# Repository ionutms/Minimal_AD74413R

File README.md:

# Minimal_AD74413R

## Overview

This repository contains a minimal KiCad design project for the Analog Devices AD74413R, a quad-channel, software-configurable input and output device. The project includes schematic designs and PCB layout files for implementing this versatile analog I/O device.

## Disclaimer

> [!NOTE]
> This project is provided "as is" and without any warranty, express or implied. For more details, please see the [LICENSE](LICENSE) file.

## About the AD74413R

The AD74413R from Analog Devices is a quad-channel, software-configurable input/output solution for building and process control applications. It integrates a 16-bit, sigma-delta (Σ-Δ) analog-to-digital converter (ADC) and four 13-bit digital-to-analog converters (DACs).

Key features include:

- **Software-Configurable Channels:** Each of the four channels can be independently configured as:
  - Analog Input (Voltage or Current)
  - Analog Output (Voltage or Current)
  - Digital Input
  - Resistance Temperature Detector (RTD) and Thermocouple measurements
- **Multiple Operating Modes:**
  - Voltage Output: 0 V to 10 V
  - Current Output: 0 mA to 24 mA
  - Voltage Input: ±10 V
  - Current Input: 0 mA to 24 mA (externally powered and loop-powered)
  - Digital Input: Logic and loop-powered
- **High Accuracy:** Includes a high-accuracy 2.5V internal reference.
- **Robustness and Diagnostics:** Features on-chip diagnostics like open-circuit and short-circuit detection.
- **HART Compatibility:** Compatible with HART (Highway Addressable Remote Transducer) protocol.
- **Communication:** Uses a Serial Peripheral Interface (SPI) for configuration and data transfer.
- **Operating Temperature Range:** -40°C to +105°C.

## Project Structure

```
minimal_ad74413r/
├── minimal_ad74413r.kicad_sch       # Main schematic file
├── minimal_ad74413r.kicad_pcb       # PCB layout file
├── minimal_ad74413r.kicad_pro       # Project configuration file
├── fp-lib-table                     # Footprint library table
├── sym-lib-table                    # Symbol library table
├── Front End Channel 1.kicad_sch    # Channel-specific schematic
├── project_jobs_set.kicad_jobset    # Project job settings
├── ibom.config.ini                  # Interactive BOM configuration
├── docs/                            # Documentation files
│   ├── pictures/                    # Images and photos
│   ├── schematics/                  # Schematic PDF exports
│   └── 3d_models/                   # 3D model files
└── KiCAD_Symbols_Generator/         # Submodule for symbol generation from CSV data
```

## Project Features

This design provides a minimal implementation of the AD74413R with the following features:

- **Power Supply:**
  - AVDD: +24V
  - AVSS: -24V
  - IOVDD: +3.3V
  - AVDD_REG and DVDD_REG: +1.8V (internally regulated)
- **Channel Configuration:**
  - Basic protection circuits for each of the four I/O channels.
  - Support for all operating modes of the AD74413R.
- **Bill of Materials (BOM):**
  - Interactive HTML BOM (`ibom.html`) for easy component identification and sourcing.
- **Libraries:**
  - Comprehensive symbol and footprint libraries integrated as a submodule.
- **3D Model:**
  - Includes a 3D model of the board for better visualization.

## Getting Started

### Prerequisites

- [KiCad EDA](https://www.kicad.org/) version 9.0 or later installed on your system
- Git (for cloning the repository and submodule management)

### Opening the Project

1. **Clone the repository** (including submodules):
   ```bash
   git clone --recursive https://github.com/ionutms/Minimal_AD74413R.git
   ```
   
   If you've already cloned the repository without submodules, initialize them with:
   ```bash
   git submodule init
   git submodule update
   ```

2. **Open the project in KiCad**:
   - Launch KiCad
   - Click "Open Existing Project"
   - Navigate to the cloned repository folder
   - Select the `minimal_ad74413r.kicad_pro` file

3. **Explore the design**:
   - Open the schematic editor to view the circuit design
   - Open the PCB editor to view the board layout
   - Review the symbol and footprint libraries used in the design

### Project Files

- **Main schematic**: `minimal_ad74413r.kicad_sch` - Contains the primary circuit design with the AD74413R and support components
- **Channel schematic**: `Front End Channel 1.kicad_sch` - Detailed implementation of one channel with protection and filtering
- **PCB layout**: `minimal_ad74413r.kicad_pcb` - Physical board design file with proper component placement
- **Project configuration**: `minimal_ad74413r.kicad_pro` - KiCad project settings

## Dependencies

This project has the following dependencies:

### 1. KiCAD Symbols Generator

This repository uses [KiCAD_Symbols_Generator](https://github.com/ionutms/KiCAD_Symbols_Generator) as a submodule for custom symbol generation.

To initialize the submodule after cloning this repository:

```bash
git submodule update --init --recursive
```

### 2. 3D Models

This project requires the [3D_Models_Vault](https://github.com/ionutms/3D_Models_Vault) repository for 3D models.

#### Setup for KiCAD 9:

1. Clone the 3D models repository:
   ```bash
   git clone https://github.com/ionutms/3D_Models_Vault.git
   ```

2. In KiCAD 9, add an environment variable:
   - Variable name: `KICAD9_3D_MODELS_VAULT`
   - Variable value: Full path to where you cloned the 3D_Models_Vault repository

## Usage

After setting up the dependencies, open the project in KiCad 9 to access all features including the 3D models.

## Symbol Generator Submodule

This project includes the KiCAD_Symbols_Generator as a submodule, which provides tools for generating KiCad symbols from CSV data files. For more information on using this tool, see the [KiCAD_Symbols_Generator documentation](minimal_ad74413r/KiCAD_Symbols_Generator/README.md).

## Documentation

The `docs` folder contains:
- Schematic PDF exports
- Images and photos of the design
- 3D model files (GLB and WRL formats)

## Visuals

The following images showcase the PCB design from different perspectives:

*Top View of the PCB*

*Side View of the PCB*

*Bottom View of the PCB*

## License

This project is licensed under the MIT License - see the [LICENSE](LICENSE) file for details.

## References

- [AD74413R Datasheet](https://www.analog.com/media/en/technical-documentation/data-sheets/ad74413r.pdf)
- [KiCad EDA](https://www.kicad.org/)

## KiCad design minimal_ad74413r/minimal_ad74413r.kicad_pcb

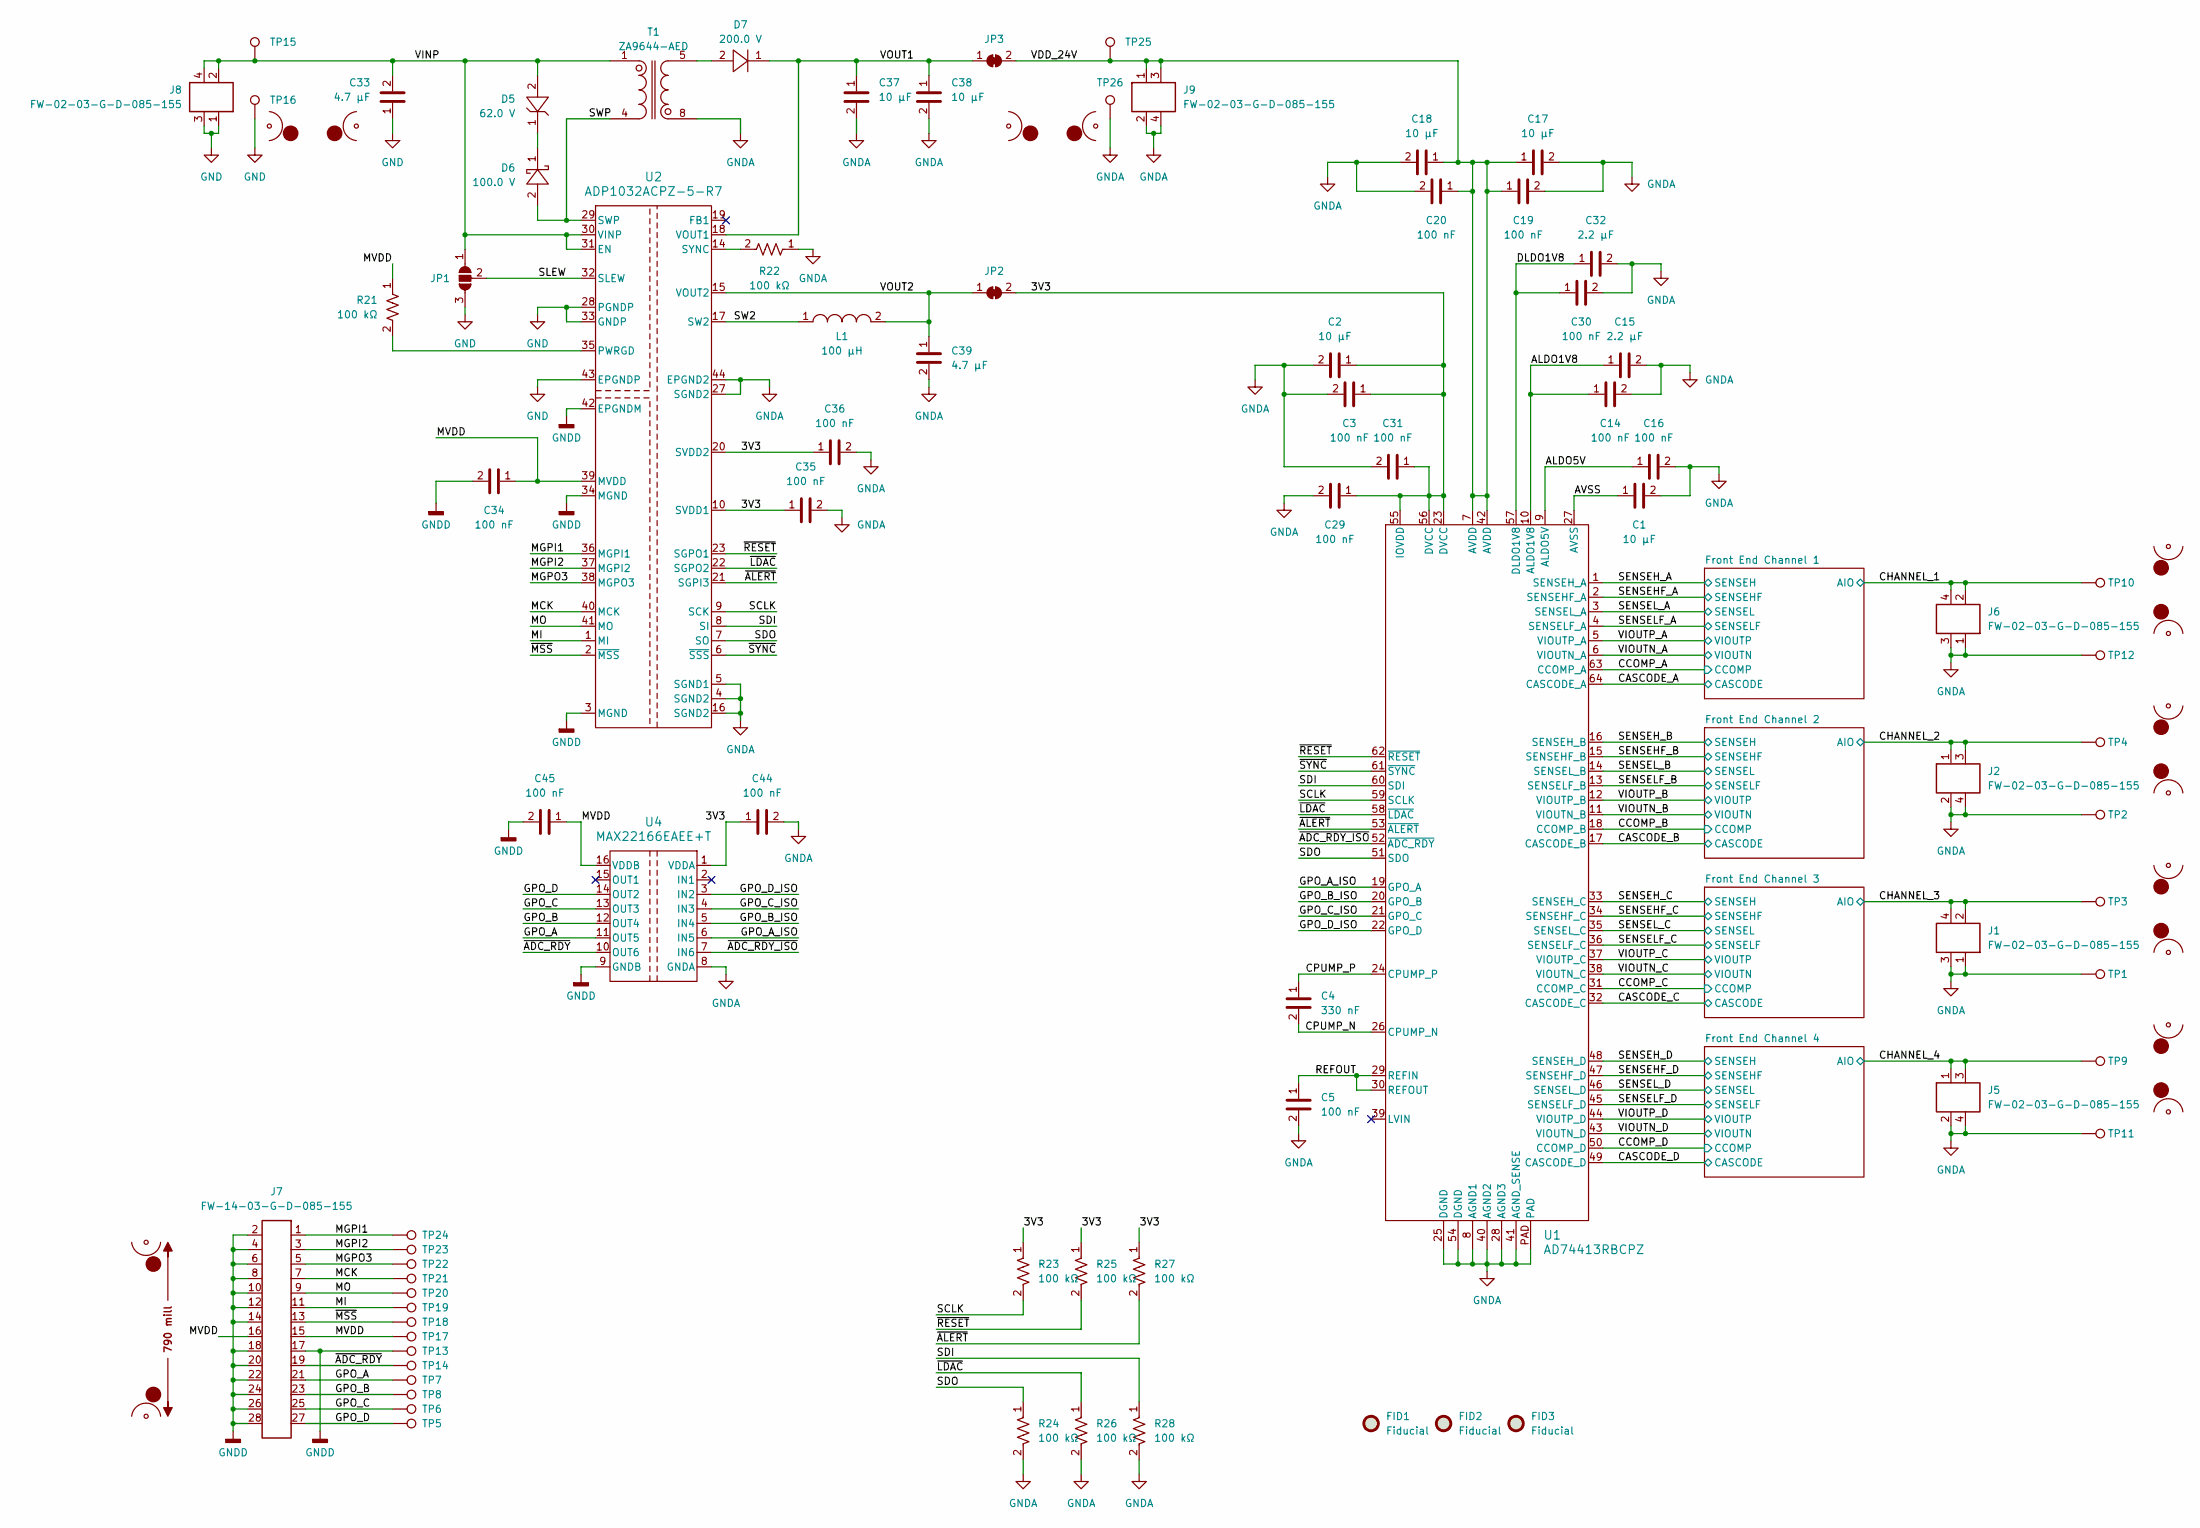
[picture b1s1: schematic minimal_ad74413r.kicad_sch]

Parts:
C1, C2, C17, C18, C37, C38: 10 µF; C_1206_3216Metric; Voltage Rating DC 50 VDC; Tolerance 10%; MPN CL31B106KBHNNN#
C3, C5, C14, C16, C19, C20, C29, C30, C31, C34, C35, C36, C44, C45: 100 nF; C_0402_1005Metric; Voltage Rating DC 50 VDC; Tolerance 10%; MPN GCM155R71H104KE02D
C4: 330 nF; C_0603_1608Metric; Voltage Rating DC 10 VDC; Tolerance 10%; MPN GRM188R71A334KA61D
C15, C32: 2.2 µF; C_0402_1005Metric; Voltage Rating DC 10 VDC; Tolerance 10%; MPN GRM155Z71A225KE44D
C33: 4.7 µF; C_1210_200_3225Metric; Tolerance 10%; Voltage Rating 100V; MPN GCM32DC72A475KE02K
C39: 4.7 µF; C_0603_1608Metric; Voltage Rating DC 10 VDC; Tolerance 10%; MPN C1608X7S1A475K080AC
D5: 62.0 V; SOD_123; MPN MMSZ5265BT1G
D6: 100.0 V; PowerDI_123; MPN DFLS1200-7
D7: 200.0 V; SOD_123F; MPN US1DWF
FID1, FID2, FID3: Fiducial; Fiducial_0.5mm_Mask1mm
J1, J2, J5, J6, J8, J9: FW-02-03-G-D-085-155; Current Rating (A) 5.2; Voltage Rating (V) 300; MPN FW-02-03-G-D-085-155
J7: FW-14-03-G-D-085-155; Current Rating (A) 5.2; Voltage Rating (V) 300; MPN FW-14-03-G-D-085-155
JP1: SolderJumper_3_Open; SolderJumper-3_P1.3mm_Open_RoundedPad1.0x1.5mm_NumberLabels
JP2, JP3: SolderJumper_2_Bridged; SolderJumper-2_P1.3mm_Bridged_RoundedPad1.0x1.5mm
L1: 100 µH; XFL3012; Tolerance ±20%; MPN XFL3012-104ME
MB1, MB2, MB5, MB6, MB8, MB9: mouse-bite-midle-50mil-200mil
MB7: mouse-bite-midle-50mil-200mil; mouse-bite-50mil-790mil
R21, R22, R23, R24, R25, R26, R27, R28: 100 kΩ; R_0402_1005Metric; Voltage Rating 50V; Tolerance 5%; MPN ERJ-2GEJ104X
T1: ZA9644-AED; ZA9644; Tolerance ±10%; MPN ZA9644-AED
TP1, TP2, TP3, TP4, TP5, TP6, TP7, TP8, TP9, TP10, TP11, TP12, TP13, TP14, TP15, TP16, TP17, TP18, TP19, TP20, TP21, TP22, TP23, TP24, TP25, TP26: TestPoint; TestPoint_THTPad_Castelated
U1: AD74413RBCPZ; CP-64-15_ADI; MPN AD74413RBCPZ
U2: ADP1032ACPZ-5-R7; CP-41-1_ADI; MPN ADP1032ACPZ-5-R7
U4: MAX22166EAEE+T; 21-0055_E16MS&plus_2_MXM_ADI; MPN MAX22166EAEE+T

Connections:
/3V3: C2.1, C3.1, C29.1, C31.1, C35.1, C36.1, C44.1, JP2.2, R23.1, R25.1, R27.1, U1.23 (DVCC), U1.55 (IOVDD), U1.56 (DVCC), U2.10 (SVDD1), U2.20 (SVDD2), U4.1 (VDDA)
/ALDO1V8: C14.1, C15.1, U1.10 (ALDO1V8)
/ALDO5V: C16.1, U1.9 (ALDO5V)
/AVSS: C1.1, U1.27 (AVSS)
/CASCODE_A: U1.64 (CASCODE_A); also elsewhere on the board
/CASCODE_B: U1.17 (CASCODE_B); also elsewhere on the board
/CASCODE_C: U1.32 (CASCODE_C); also elsewhere on the board
/CASCODE_D: U1.49 (CASCODE_D); also elsewhere on the board
/CCOMP_A: U1.63 (CCOMP_A); also elsewhere on the board
/CCOMP_B: U1.18 (CCOMP_B); also elsewhere on the board
/CCOMP_C: U1.31 (CCOMP_C); also elsewhere on the board
/CCOMP_D: U1.50 (CCOMP_D); also elsewhere on the board
/CHANNEL_1: J6.2, J6.4, TP10.1; also elsewhere on the board
/CHANNEL_2: J2.1, J2.3, TP4.1; also elsewhere on the board
/CHANNEL_3: J1.2, J1.4, TP3.1; also elsewhere on the board
/CHANNEL_4: J5.1, J5.3, TP9.1; also elsewhere on the board
/CPUMP_N: C4.2, U1.26 (CPUMP_N)
/CPUMP_P: C4.1, U1.24 (CPUMP_P)
/DLDO1V8: C30.1, C32.1, U1.57 (DLDO1V8)
/GPO_A: J7.21, TP7.1, U4.11 (OUT5)
/GPO_A_ISO: U1.19 (GPO_A), U4.6 (IN5)
/GPO_B: J7.23, TP8.1, U4.12 (OUT4)
/GPO_B_ISO: U1.20 (GPO_B), U4.5 (IN4)
/GPO_C: J7.25, TP6.1, U4.13 (OUT3)
/GPO_C_ISO: U1.21 (GPO_C), U4.4 (IN3)
/GPO_D: J7.27, TP5.1, U4.14 (OUT2)
/GPO_D_ISO: U1.22 (GPO_D), U4.3 (IN2)
/MCK: J7.7, TP21.1, U2.40 (MCK)
/MGPI1: J7.1, TP24.1, U2.36 (MGPI1)
/MGPI2: J7.3, TP23.1, U2.37 (MGPI2)
/MGPO3: J7.5, TP22.1, U2.38 (MGPO3)
/MI: J7.11, TP19.1, U2.1 (MI)
/MO: J7.9, TP20.1, U2.41 (MO)
/MVDD: C34.1, C45.1, J7.15, J7.16, R21.1, TP17.1, U2.39 (MVDD), U4.16 (VDDB)
/REFOUT: C5.1, U1.29 (REFIN), U1.30 (REFOUT)
/SCLK: R23.2, U1.59 (SCLK), U2.9 (SCK)
/SDI: R28.1, U1.60 (SDI), U2.8 (SI)
/SDO: R24.1, U1.51 (SDO), U2.7 (SO)
/SENSEHF_A: U1.2 (SENSEHF_A); also elsewhere on the board
/SENSEHF_B: U1.15 (SENSEHF_B); also elsewhere on the board
/SENSEHF_C: U1.34 (SENSEHF_C); also elsewhere on the board
/SENSEHF_D: U1.47 (SENSEHF_D); also elsewhere on the board
/SENSEH_A: U1.1 (SENSEH_A); also elsewhere on the board
/SENSEH_B: U1.16 (SENSEH_B); also elsewhere on the board
/SENSEH_C: U1.33 (SENSEH_C); also elsewhere on the board
/SENSEH_D: U1.48 (SENSEH_D); also elsewhere on the board
/SENSELF_A: U1.4 (SENSELF_A); also elsewhere on the board
/SENSELF_B: U1.13 (SENSELF_B); also elsewhere on the board
/SENSELF_C: U1.36 (SENSELF_C); also elsewhere on the board
/SENSELF_D: U1.45 (SENSELF_D); also elsewhere on the board
/SENSEL_A: U1.3 (SENSEL_A); also elsewhere on the board
/SENSEL_B: U1.14 (SENSEL_B); also elsewhere on the board
/SENSEL_C: U1.35 (SENSEL_C); also elsewhere on the board
/SENSEL_D: U1.46 (SENSEL_D); also elsewhere on the board
/SLEW: JP1.2 (C), U2.32 (SLEW)
/SW2: L1.1, U2.17 (SW2)
/SWP: D6.2, T1.4, U2.29 (SWP)
/VDD_24V: C17.1, C18.1, C19.1, C20.1, J9.1, J9.3, JP3.2, TP25.1, U1.7 (AVDD), U1.42 (AVDD)
/VINP: C33.2, D5.2, J8.2, J8.4, JP1.1 (A), T1.1, TP15.1, U2.30 (VINP), U2.31 (EN)
/VIOUTN_A: U1.6 (VIOUTN_A); also elsewhere on the board
/VIOUTN_B: U1.11 (VIOUTN_B); also elsewhere on the board
/VIOUTN_C: U1.38 (VIOUTN_C); also elsewhere on the board
/VIOUTN_D: U1.43 (VIOUTN_D); also elsewhere on the board
/VIOUTP_A: U1.5 (VIOUTP_A); also elsewhere on the board
/VIOUTP_B: U1.12 (VIOUTP_B); also elsewhere on the board
/VIOUTP_C: U1.37 (VIOUTP_C); also elsewhere on the board
/VIOUTP_D: U1.44 (VIOUTP_D); also elsewhere on the board
/VOUT1: C37.1, C38.1, D7.1, JP3.1, U2.18 (VOUT1)
/VOUT2: C39.1, JP2.1, L1.2, U2.15 (VOUT2)
/~ADC_RDY_ISO: U1.52 (~ADC_RDY), U4.7 (IN6)
/~ADC_RDY: J7.19, TP14.1, U4.10 (OUT6)
/~ALERT: R27.2, U1.53 (~ALERT), U2.21 (SGPI3)
/~LDAC: R26.1, U1.58 (~LDAC), U2.22 (SGPO2)
/~MSS: J7.13, TP18.1, U2.2 (~MSS)
/~RESET: R25.2, U1.62 (~RESET), U2.23 (SGPO1)
/~SYNC: U1.61 (~SYNC), U2.6 (~SSS)
GND: C33.1, J8.1, J8.3, JP1.3 (B), TP16.1, U2.28 (PGNDP), U2.33 (GNDP), U2.43 (EPGNDP)
GNDA: C1.2, C2.2, C3.2, C5.2, C14.2, C15.2, C16.2, C17.2, C18.2, C19.2, C20.2, C29.2, C30.2, C31.2, C32.2, C35.2, C36.2, C37.2, C38.2, C39.2, C44.2, J1.1, J1.3, J2.2, J2.4, J5.2, J5.4, J6.1, J6.3, J9.2, J9.4, R22.1, R24.2, R26.2, R28.2, T1.8, TP1.1, TP2.1, TP11.1, TP12.1, TP26.1, U1.8 (AGND1), U1.25 (DGND), U1.28 (AGND3), U1.40 (AGND2), U1.41 (AGND_SENSE), U1.54 (DGND), U1.PAD, U2.4 (SGND2), U2.5 (SGND1), U2.16 (SGND2), U2.27 (SGND2), U2.44 (EPGND2), U4.8 (GNDA); also elsewhere on the board
GNDD: C34.2, C45.2, J7.2, J7.4, J7.6, J7.8, J7.10, J7.12, J7.14, J7.17, J7.18, J7.20, J7.22, J7.24, J7.26, J7.28, TP13.1, U2.3 (MGND), U2.34 (MGND), U2.42 (EPGNDM), U4.9 (GNDB)
unnamed: D5.1, D6.1
unnamed: D7.2, T1.5
unnamed: R21.2, U2.35 (PWRGD)
unnamed: R22.2, U2.14 (SYNC)

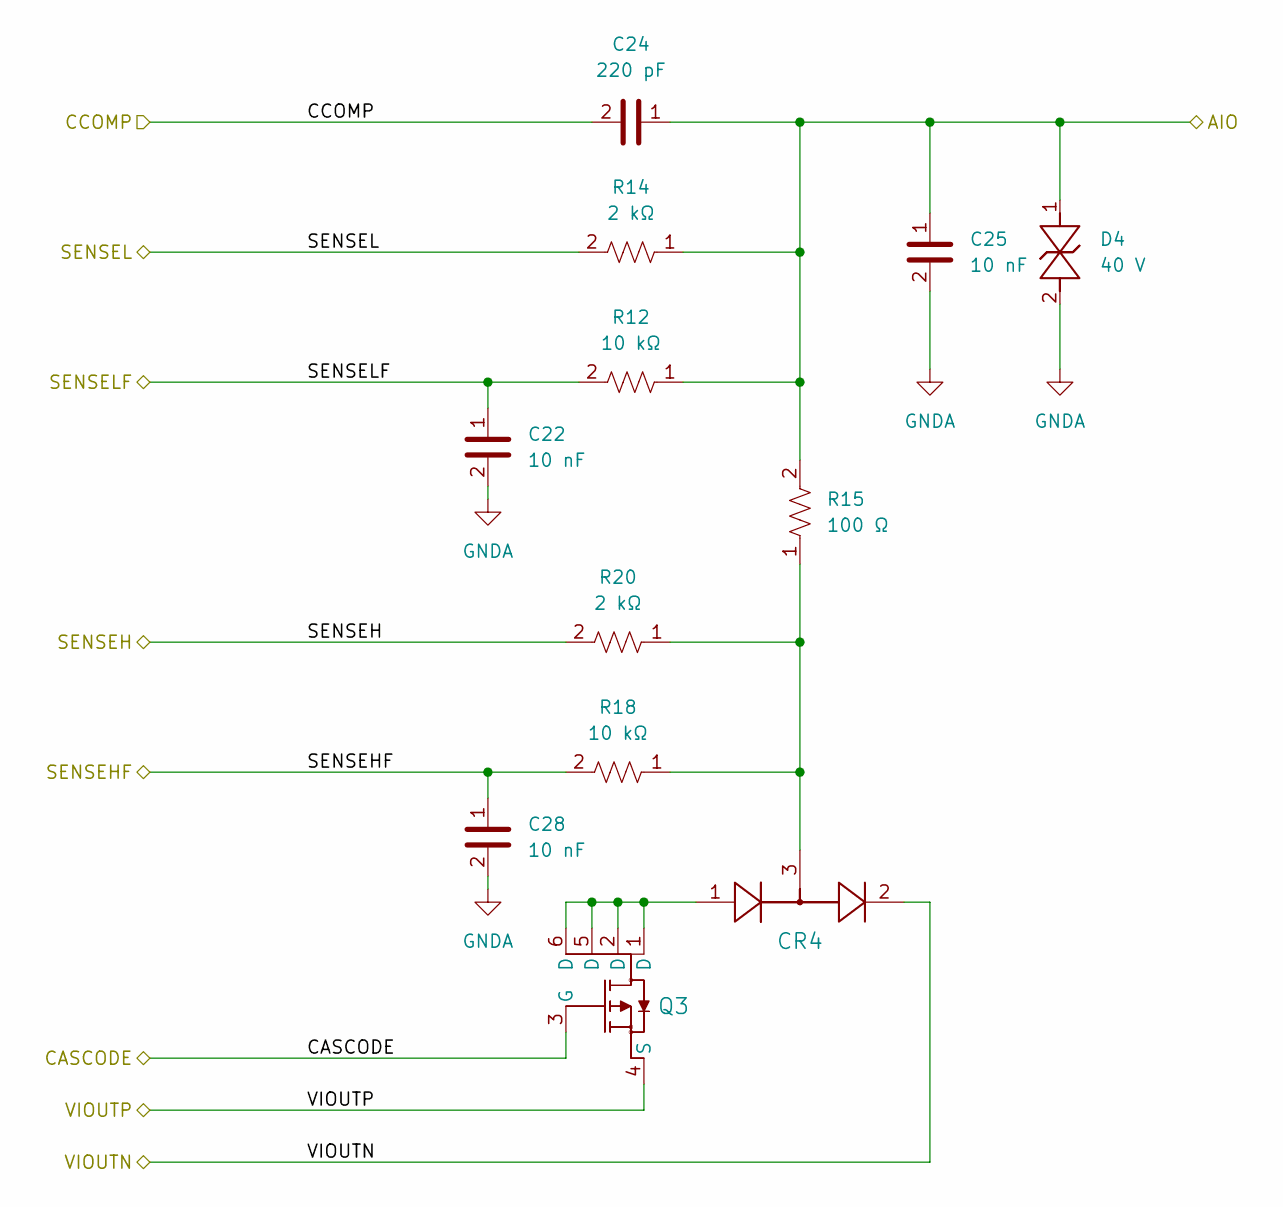
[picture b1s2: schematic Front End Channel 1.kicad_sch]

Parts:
C22, C25, C28: 10 nF; C_0402_1005Metric; Voltage Rating DC 100 VDC; Tolerance 10%; MPN C1005X7S2A103K050BB
C24: 220 pF; C_0402_1005Metric; Voltage Rating DC 100 VDC; Tolerance 5%; MPN CGA2B2NP02A221J050BA
CR4: 100 V; SC_70; MPN SBAV99WT1G
D4: 40 V; DO-214AB-2; MPN SMCJ40A/CA
Q3: -60 V; SOT-26; MPN ZXMP6A17E6TA
R12, R18: 10 kΩ; R_0402_1005Metric; Voltage Rating 50V; Tolerance 1%; MPN ERJ-2RKF1002X
R14: 2 kΩ; R_0402_1005Metric; Voltage Rating 50V; Tolerance 1%; MPN ERJ-2RKF2001X
R15: 100 Ω; R_0805_2012Metric; Voltage Rating 150V; Tolerance 0.1%; MPN RT0805BRB07100RL
R20: 2 kΩ; R_0402_1005Metric; Voltage Rating 50V; Tolerance 0.1%; MPN ERA-2AEB202X

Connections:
/CASCODE_A: Q3.3 (G); also elsewhere on the board
/CCOMP_A: C24.2; also elsewhere on the board
/CHANNEL_1: C24.1, C25.1, D4.1, R12.1, R14.1, R15.2; also elsewhere on the board
/SENSEHF_A: C28.1, R18.2; also elsewhere on the board
/SENSEH_A: R20.2; also elsewhere on the board
/SENSELF_A: C22.1, R12.2; also elsewhere on the board
/SENSEL_A: R14.2; also elsewhere on the board
/VIOUTN_A: CR4.2; also elsewhere on the board
/VIOUTP_A: Q3.4 (S); also elsewhere on the board
GNDA: C22.2, C25.2, C28.2, D4.2; also elsewhere on the board
unnamed: CR4.1, Q3.1 (D), Q3.2 (D), Q3.5 (D), Q3.6 (D)
unnamed: CR4.3, R15.1, R18.1, R20.1

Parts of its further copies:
C6, C7, C8, C9, C12, C13, C21, C26, C27: 10 nF; C_0402_1005Metric; Voltage Rating DC 100 VDC; Tolerance 10%; MPN C1005X7S2A103K050BB
C10, C11, C23: 220 pF; C_0402_1005Metric; Voltage Rating DC 100 VDC; Tolerance 5%; MPN CGA2B2NP02A221J050BA
CR1, CR2, CR3: 100 V; SC_70; MPN SBAV99WT1G
D1, D2, D3: 40 V; DO-214AB-2; MPN SMCJ40A/CA
Q1, Q2, Q4: -60 V; SOT-26; MPN ZXMP6A17E6TA
R1, R2, R19: 2 kΩ; R_0402_1005Metric; Voltage Rating 50V; Tolerance 0.1%; MPN ERA-2AEB202X
R3, R4, R9, R10, R11, R17: 10 kΩ; R_0402_1005Metric; Voltage Rating 50V; Tolerance 1%; MPN ERJ-2RKF1002X
R5, R6, R16: 100 Ω; R_0805_2012Metric; Voltage Rating 150V; Tolerance 0.1%; MPN RT0805BRB07100RL
R7, R8, R13: 2 kΩ; R_0402_1005Metric; Voltage Rating 50V; Tolerance 1%; MPN ERJ-2RKF2001X

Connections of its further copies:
/CASCODE_B: Q1.3 (G); also elsewhere on the board
/CASCODE_C: Q2.3 (G); also elsewhere on the board
/CASCODE_D: Q4.3 (G); also elsewhere on the board
/CCOMP_B: C11.2; also elsewhere on the board
/CCOMP_C: C10.2; also elsewhere on the board
/CCOMP_D: C23.2; also elsewhere on the board
/CHANNEL_2: C9.1, C11.1, D2.1, R6.2, R8.1, R10.1; also elsewhere on the board
/CHANNEL_3: C8.1, C10.1, D1.1, R5.2, R7.1, R9.1; also elsewhere on the board
/CHANNEL_4: C23.1, C26.1, D3.1, R11.1, R13.1, R16.2; also elsewhere on the board
/SENSEHF_B: C7.1, R4.2; also elsewhere on the board
/SENSEHF_C: C6.1, R3.2; also elsewhere on the board
/SENSEHF_D: C27.1, R17.2; also elsewhere on the board
/SENSEH_B: R2.2; also elsewhere on the board
/SENSEH_C: R1.2; also elsewhere on the board
/SENSEH_D: R19.2; also elsewhere on the board
/SENSELF_B: C13.1, R10.2; also elsewhere on the board
/SENSELF_C: C12.1, R9.2; also elsewhere on the board
/SENSELF_D: C21.1, R11.2; also elsewhere on the board
/SENSEL_B: R8.2; also elsewhere on the board
/SENSEL_C: R7.2; also elsewhere on the board
/SENSEL_D: R13.2; also elsewhere on the board
/VIOUTN_B: CR2.2; also elsewhere on the board
/VIOUTN_C: CR1.2; also elsewhere on the board
/VIOUTN_D: CR3.2; also elsewhere on the board
/VIOUTP_B: Q1.4 (S); also elsewhere on the board
/VIOUTP_C: Q2.4 (S); also elsewhere on the board
/VIOUTP_D: Q4.4 (S); also elsewhere on the board
GNDA: C6.2, C7.2, C8.2, C9.2, C12.2, C13.2, C21.2, C26.2, C27.2, D1.2, D2.2, D3.2; also elsewhere on the board
unnamed: CR1.1, Q2.1 (D), Q2.2 (D), Q2.5 (D), Q2.6 (D)
unnamed: CR1.3, R1.1, R3.1, R5.1
unnamed: CR2.1, Q1.1 (D), Q1.2 (D), Q1.5 (D), Q1.6 (D)
unnamed: CR2.3, R2.1, R4.1, R6.1
unnamed: CR3.1, Q4.1 (D), Q4.2 (D), Q4.5 (D), Q4.6 (D)
unnamed: CR3.3, R16.1, R17.1, R19.1

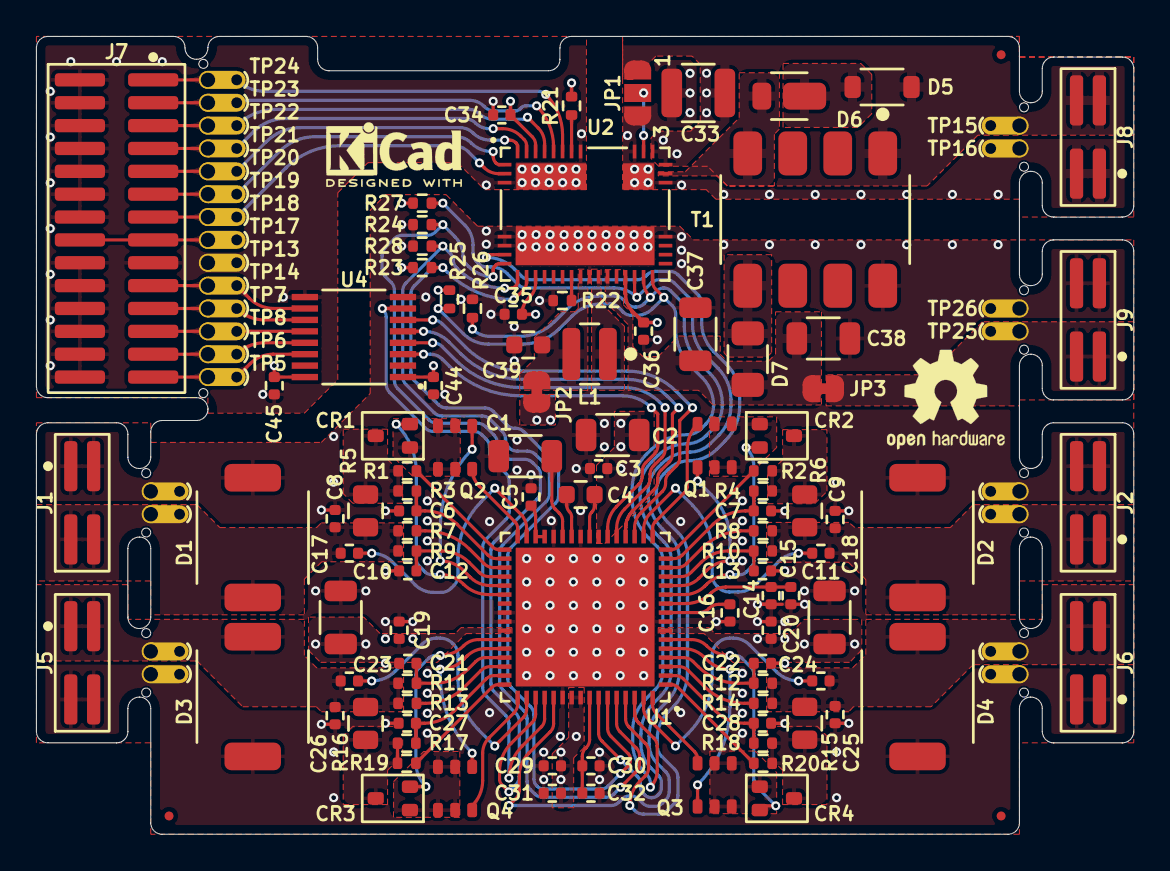
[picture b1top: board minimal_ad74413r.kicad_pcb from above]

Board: 4 copper layers, 61.0 x 44.3 mm, 135 parts (0 on the bottom side), 91 nets.

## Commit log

2025-01-22 Add the initial Kicad project
2025-01-22 Add KiCAD_Symbol_Generator as submodule
2025-01-22 setup libraries
2025-01-23 backup
2025-01-26 Minor updates
2025-01-28 Update references in schematic and update subproject commit
2025-01-29 Update VRML file reference in project configuration
2025-01-30 Minor updates to project files
2025-01-30 Update subproject commit and add mouse bite footprints to fp-lib-table
2025-01-31 Update subproject commit in KiCAD_Symbol_Generator
2025-02-03 Update project files and improve organization
2025-02-07 Update subproject commit and add new configuration and library entries for KiCAD_Symbol_Generator
2025-02-08 Add GLB 3D model
2025-03-01 Update subproject commit and add new library entries for KiCAD_Symbol_Generator
2025-03-02 Update project files and enhance structure
2025-03-02 Update reference properties in minimal_ad74413r schematic
2025-03-04 Update GLB 3D model for minimal_ad74413r
2025-03-10 Update subproject commit for KiCAD_Symbol_Generator
2025-03-16 Remove KiCAD_Symbol_Generator submodule reference
2025-03-16 Add KiCAD_Symbols_Generator submodule for minimal_ad74413r
2025-03-16 Update footprint library URIs to use KiCAD_Symbols_Generator
2025-03-18 Switch to KiCad 9
2025-03-19 Add .log files to .gitignore
2025-03-19 Add project job set configuration for minimal_ad74413r
2025-03-19 Add minimal_ad74413r side image and update project configuration for .glb step file
2025-03-19 Refactor project job set for minimal_ad74413r to streamline GLB export settings
2025-03-19 Update minimal_ad74413r .glb and side image files
2025-03-20 Add output filename and new render command to project job set for minimal_ad74413r
2025-03-20 Update subproject commit reference for KiCAD Symbols Generator
2025-03-20 Add top image and update dimensions in KiCAD project for minimal_ad74413r
2025-03-21 Update project job set for minimal_ad74413r to enhance export commands and output organization
2025-03-21 Remove obsolete top and side images; add new 3D model and updated picture files for minimal_ad74413r
2025-03-22 Update README.md to include project dependencies and setup instructions for KiCAD and 3D models
2025-04-05 Development backup
2025-04-05 Update 3D files and images
2025-04-06 Add schematic export job and output folder for minimal_ad74413r
2025-04-06 Add schematic PDF for minimal_ad74413r
2025-04-06 Update 3D models and images for minimal_ad74413r documentation
2025-04-07 Update subproject commit for KiCAD Symbols Generator
2025-04-07 Update schematic PDF for minimal_ad74413r with new components and layout adjustments
2025-04-08 update ibom
2025-04-08 Update schematic PDF for minimal_ad74413r with layout enhancements and component adjustments
2025-04-11 Update schematic PDF for minimal_ad74413r
2025-04-14 update minimal_ad74413r footprint
2025-04-18 Update KiCad documentation (schematics and PCB renders)
2025-04-18 Add configuration file for default zoom factor and update workflow to use it
2025-04-19 Add Gruvbox theme support for KiCad PDF export
2025-04-23 Remove unused rendering jobs from project_jobs_set.kicad_jobset
2025-04-23 Refactor KiCad configuration handling and update documentation generation workflow
2025-04-23 cleanup
2025-04-23 Update KiCad documentation for minimal_ad74413r (schematics and PCB renders)
2025-04-23 Update KiCad configuration for improved rendering quality and adjust zoom/pan settings
2025-04-24 Enhance KiCad job generation workflow with improved configuration extraction and 3D model handling
2025-05-23 Add GitHub Actions workflow to generate KiCad 3D models
2025-05-25 Update trigger branch for KiCad 3D models generation workflow
2025-08-18 Add bottom view rendering to KiCad workflow and update configuration
2025-08-20 Update README.md with more accurate project information and improved documentation
2025-08-20 Remove outdated PDF documentation
2025-08-22 Update KiCad workflow configurations
2025-08-28 Update KiCad workflows to use newer Docker image and add Interactive HTML BOM generation
2025-09-02 docs: Update and improve README.md
2025-10-05 chore: update workflows from central repository
2025-10-05 chore: update workflows and kicad config from central repository
2025-10-26 Update kicad-config workflow settings
